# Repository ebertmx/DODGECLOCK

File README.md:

# DCLK_MK4

A shot clock system for competitve dodgeball. The system consists of two devices: display and controller.

## Status
This project is in progress...

### Controller
A first iteration PCB was order and successfully programmed. The firmware was tested with the MCU powered externally (without battery or linear regulator).

#### Problem with Linear Regulator
The BLE functionality on the PCB was not functional when powered by battery. Trouble shooting revealed the linear regulator is not acceptable for the current requirement of the antenna. Voltage spike when the antenna turns on crash the MCU.

A second iteration board is in progress to improve performance and fix the power delivery problems.

### Display
The display 7-segment frame was pritned with TPU and succesffuly passed all impact tests.
A nrf52 dongle will be used as the MCU for the display to save on time, costs, and assembly requirements.
The LED strip, power supply, and nrf52 dongle have been tested in a bench top environment succeffully.

## Description
### Controller
The controller device includes
- A PCB and MCU with BLE capabilities
- An LCD
- Several user inputs
- a buzzer

The controller devices is held by the ref and used to control the shot clock count. 

The device acts as a peripheral/server. It accepts secure connections and provide clock and state information. This device is battery powered; thus, it tries to mimize power at all times. The device prioritizes the built in LCD and user controls over the BLE connection; consequently, the ref always knows the correct shot clock time and can control the state.

### Display
The display device includes
- a WS2813B LED strip formed into a 7-segment pattern
- A PCB and MCU with BLE capablilities
- 2 user buttons for pairing and mode seletion
- A power supply

The display device is plugged into a wall outlet or similar power source and mounted within view of the court. The players and ref can reference this display. 

This device acts as a central/client. It initiates a secure connection with the controller and recieves time and state information if possible. If a connection is lost of cannot be estabilished it enters a dormant state and displays nothing. Otherwise, it displays the current count down time from the controller.

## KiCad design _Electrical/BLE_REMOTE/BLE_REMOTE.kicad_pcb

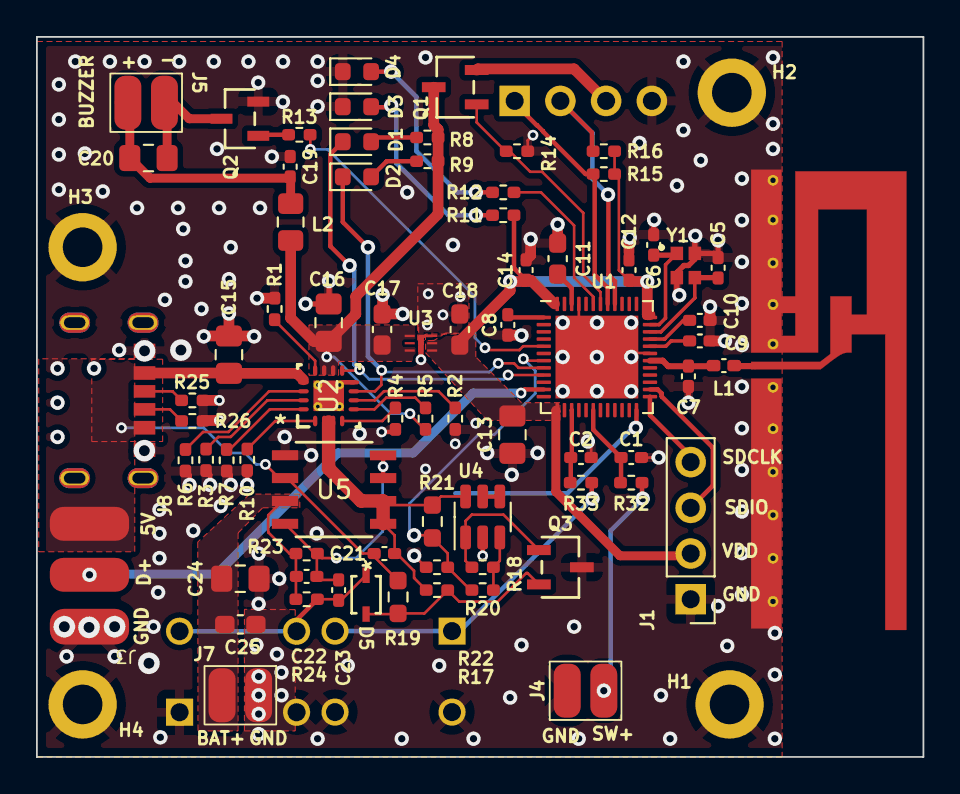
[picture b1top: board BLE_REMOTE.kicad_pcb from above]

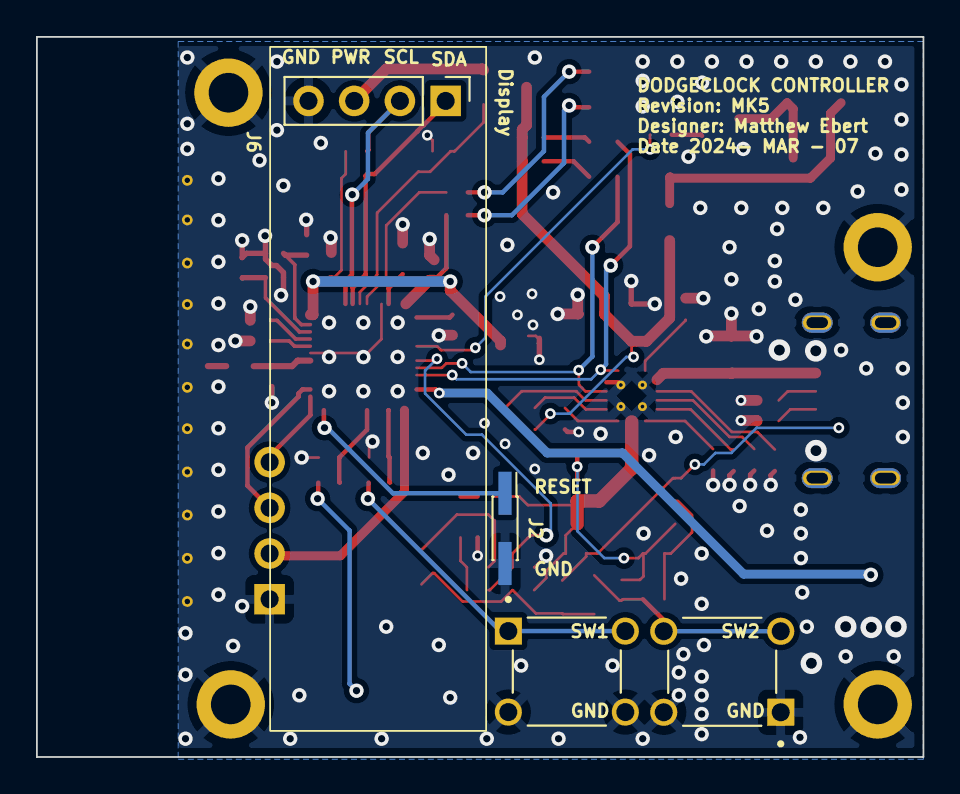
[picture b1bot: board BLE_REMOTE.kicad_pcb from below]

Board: 4 copper layers, 49.3 x 40.0 mm, 82 parts (4 on the bottom side), 54 nets.

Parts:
A1: SWRU120B
C1, C2, C21: 10uF; C_0402_1005Metric_Pad0.74x0.62mm_HandSolder
C5, C6: 10pF; C_0402_1005Metric_Pad0.74x0.62mm_HandSolder
C7: 0.8pF; C_0402_1005Metric_Pad0.74x0.62mm_HandSolder
C8, C12, C14, C22: 100nF; C_0402_1005Metric_Pad0.74x0.62mm_HandSolder
C9: NC; C_0402_1005Metric_Pad0.74x0.62mm_HandSolder
C10: 100pF; C_0402_1005Metric_Pad0.74x0.62mm_HandSolder
C11: 1uF; C_0603_1608Metric_Pad1.08x0.95mm_HandSolder
C13, C16, C20, C24: 4.7uF; C_0805_2012Metric_Pad1.18x1.45mm_HandSolder
C15: 1uF; C_0805_2012Metric_Pad1.18x1.45mm_HandSolder
C17, C18, C25: 2.2uF; C_0603_1608Metric_Pad1.08x0.95mm_HandSolder
C19: 1nF; C_0402_1005Metric_Pad0.74x0.62mm_HandSolder
C23: 1uF; C_0402_1005Metric_Pad0.74x0.62mm_HandSolder
D1, D2, D3, D4: LED; LED_0603_1608Metric
D5: 1N4148WX-TP; CR_SOD323_MCC-L
H1, H2, H3, H4: MountingHole_Pad; MountingHole_2.2mm_M2_DIN965_Pad
J1: PGRM; PinHeader_1x04_P2.54mm_Vertical
J2: RESET; PinHeader_2x01_P1.27mm_Vertical_SMD
J3: LED_STRIP; 3pad_conn
J4: SWITCH; 2pad_conn_sm
J5: BUZZER; 2pad_conn_sm
J6: Display; OLED_091
J7: Battery; 2pad_conn_sm
J8: USBC; GCT_USB4125-GF-A_REVA2
L1: 3.8nH; L_0402_1005Metric_Pad0.77x0.64mm_HandSolder
L2: 10uH; L_0805_2012Metric_Pad1.15x1.40mm_HandSolder
Q1: BSS806NEH6327XTSA1; SOT-23-3L_AOS
Q2: NPN; TRAN_SS8050-G_CIP
Q3: PMOS; SOT-23-3L_AOS
R1: 2.94k; R_0402_1005Metric_Pad0.72x0.64mm_HandSolder
R2, R3, R4, R5, R6: 0R; R_0402_1005Metric_Pad0.72x0.64mm_HandSolder
R7: 4.32k; R_0402_1005Metric_Pad0.72x0.64mm_HandSolder
R8, R9, R11, R12, R32, R33: 2k; R_0402_1005Metric_Pad0.72x0.64mm_HandSolder
R10, R24: 10k; R_0402_1005Metric_Pad0.72x0.64mm_HandSolder
R13: 220; R_0402_1005Metric_Pad0.72x0.64mm_HandSolder
R14, R15, R16: 47k; R_0402_1005Metric_Pad0.72x0.64mm_HandSolder
R17, R18, R22, R23: 100k; R_0402_1005Metric_Pad0.72x0.64mm_HandSolder
R19: 300k; R_0603_1608Metric_Pad0.98x0.95mm_HandSolder
R20: 1k; R_0402_1005Metric_Pad0.72x0.64mm_HandSolder
R21: 150k; R_0603_1608Metric_Pad0.98x0.95mm_HandSolder
R25, R26: 5.1k; R_0402_1005Metric_Pad0.72x0.64mm_HandSolder
SW1, SW2: SW_Push; SW_TS02-66-120-BK-260-LCR-D
U1: nRF52832-QFxx; QFN-48-1EP_6x6mm_P0.4mm_EP4.6x4.6mm
U2: BQ24232RGTR; RGT0016C
U3: MIC5528-3.3YMT-TR; TDFN6_1P2X1P2_MCH
U4: MCP65R41; SOT-23-6
U5: IRF7319TRPBF; TRANS_IRF7103TRPBF_INF
Y1: Crystal_GND24; OSC_XRCGB32M000F2P01R0

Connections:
+5V: C15.1, C21.2, J3.3, J8.A9 (VBUS), J8.B9 (VBUS__1), R19.2, U2.13 (IN), U5.2 (G1)
/MCU/ANT: C7.1, L1.2, U1.30 (ANT)
/MCU/RESET: J2.1, U1.24 (P0.21/~RESET)
/MCU/SWDCLK: J1.4, U1.25 (SWDCLK)
/MCU/SWDIO: J1.3, U1.26 (SWDIO)
/Peripherals/BUZZ+: C19.1, C20.1, J5.2, L2.2
/Peripherals/DIS_PWR: J6.3, Q1.2 (S)
/Power/BQ_CE_N: R4.1, U2.4 (CE_N)
/Power/BQ_EN1: R2.2, U2.6 (EN1)
/Power/BQ_EN2: R5.1, U2.5 (EN2)
/Power/BQ_ILIM: R1.2, U2.12 (ILIM)
/Power/BQ_ISET: R7.2, U2.16 (ISET)
/Power/BQ_ITERM: R3.1, U2.15 (ITERM)
/Power/BQ_TMR: R6.1, U2.14 (TMR)
/Power/BQ_TS: R10.1, U2.1 (TS)
/Power/Battery/BAT+: C22.1, C24.1, C25.1, J7.2, R23.2, R24.2, U5.3 (S2)
/Power/Battery/BAT_CTRL: D5.2 (A), Q3.2 (S), R17.2, R19.1
/Power/Battery/VBAT: C21.1, R17.1, R21.1, U2.2 (BAT), U2.3 (BAT), U4.6 (V+), U5.5 (D2), U5.6 (D2)
/Power/Battery/VREF: U4.4 (-), U4.5 (Vref)
BUTTON: C2.2, R33.2, U1.15 (P0.12)
BUZZ: R13.1, U1.5 (P0.03/AIN1)
CHG_N: D1.1 (K), U1.9 (P0.07), U2.9 (CHG_N)
DIS_EN: Q1.1 (G), R14.2, U1.42 (P0.30/AIN6)
DIS_SCL: J6.2, R16.1, U1.40 (P0.28/AIN4)
DIS_SDA: J6.1, R15.1, U1.41 (P0.29/AIN5)
GND: A1.2 (GND), A1.4, A1.5, C1.1, C2.1, C5.2, C6.1, C7.2, C8.2, C9.2, C10.2, C11.2, C12.1, C13.1, C14.1, C15.2, C16.2, C17.2, C18.2, C19.2, C24.2, C25.2, D3.1 (K), D4.1 (K), H1.1, H2.1, H3.1, H4.1, J1.1, J2.2, J3.1, J4.1, J6.4, J7.1, J8.A12 (GND), J8.B12 (GND__1), J8.S1 (SHIELD), J8.S2 (SHIELD__1), J8.S3 (SHIELD__2), J8.S4 (SHIELD__3), Q2.2, Q3.3 (D), R1.1, R2.1, R3.2, R4.2, R6.2, R7.1, R10.2, R14.1, R22.2, R25.1, R26.1, SW1.3, SW1.4, SW2.1, SW2.2, U1.31 (VSS), U1.45 (VSS), U1.49 (VSS), U2.8 (VSS), U2.17 (EP), U2.V, U3.3 (GND), U3.7 (EPAD), U4.2 (V-), U5.1 (S1), Y1.2, Y1.4
LED_D: J3.2, U1.11 (NFC1/P0.09)
unnamed: A1.1 (SIG), L1.1
unnamed: D1.2 (A), R8.2
unnamed: D2.2 (A), R9.2
unnamed: D3.2 (A), R11.2
unnamed: D4.2 (A), R12.2
unnamed: C23.2, D5.1 (K), R24.1, SW2.3, SW2.4
unnamed: J4.2, R32.1
unnamed: C20.2, J5.1, Q2.3
unnamed: J8.A5 (CC1), R25.2
unnamed: J8.B5 (CC2), R26.2
unnamed: Q2.1, R13.2
unnamed: Q3.1 (G), R18.2, U4.1
unnamed: R33.1, SW1.1, SW1.2
unnamed: C8.1, U1.1 (DEC1)
unnamed: C9.1, U1.32 (DEC2)
unnamed: C10.1, U1.33 (DEC3)
unnamed: C11.1, U1.46 (DEC4)
unnamed: C5.1, U1.34 (XC1), Y1.3
unnamed: C6.2, U1.35 (XC2), Y1.1
unnamed: R18.1, R20.2, U4.3 (+)
unnamed: C22.2, C23.1, R23.1, U5.4 (G2), U5.7 (D1), U5.8 (D1)
PGOOD_N: D2.1 (K), U1.8 (P0.06), U2.7 (PGOOD_N)
SWITCH: C1.2, R32.2, U1.18 (P0.15)
TEST_BAT: R20.1, R21.2, R22.1, U1.7 (P0.05/AIN3)
USER: R12.1, U1.43 (P0.31/AIN7)
VCC: C16.1, C17.1, L2.1, Q1.3 (D), R5.2, R8.1, R9.1, U2.10 (OUT), U2.11 (OUT), U3.4 (EN), U3.6 (VIN)
VDD: C12.2, C13.2, C14.2, C18.1, J1.2, R11.1, R15.2, R16.2, U1.13 (VDD), U1.36 (VDD), U1.48 (VDD), U3.1 (VOUT), U3.2 (VOUT)

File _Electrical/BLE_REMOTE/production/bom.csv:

Designator,Footprint,Quantity,Value,LCSC Part #
A1,SWRU120B,1,SWRU120B,
"C1, C2, C21",0402,3,10uF,C15525
C10,0402,1,100pF,C1546
C11,0603,1,1uF,C15849
"C12, C14, C22, C8",0402,4,100nF,C1525
"C13, C16, C20, C24",0805,4,4.7uF,C1779
C15,0805,1,1uF,C28323
"C17, C18, C25",0603,3,2.2uF,C23630
C19,0402,1,1nF,C1523
C23,0402,1,1uF,C52923
"C5, C6",0402,2,10pF,C32949
C7,0402,1,0.8pF,C327032
C9,0402,1,NC,
"D1, D2, D3, D4",0603,4,LED,C2286
D5,CR_SOD323_MCC-L,1,1N4148WX-TP,C2128
J5,2pad_conn_sm,1,BUZZER,C2759981
J8,GCT_USB4125-GF-A_REVA2,1,USBC,
L1,0402,1,3.8nH,C412343
L2,0805,1,10uH,C1046
Q1,SOT-23-3L_AOS,1,BSS806NEH6327XTSA1,C20917
Q2,TRAN_SS8050-G_CIP,1,NPN,C2150
Q3,SOT-23-3L_AOS,1,PMOS,C15127
R1,0402,1,2.94k,C273724
"R10, R24",0402,2,10k,C25744
"R11, R12, R32, R33, R8, R9",0402,6,2k,C4109
R13,0402,1,220,C25091
"R14, R15, R16",0402,3,47k,C25792
"R17, R18, R22, R23",0402,4,100k,C25741
R19,0603,1,300k,C23024
"R2, R3, R4, R5, R6",0402,5,0R,C17168
R20,0402,1,1k,C11702
R21,0603,1,150k,C22807
"R25, R26",0402,2,5.1k,C25905
R7,0402,1,4.32k,C334698
"SW1, SW2",SW_TS02-66-120-BK-260-LCR-D,2,SW_Push,
U1,QFN-48-1EP_6x6mm_P0.4mm_EP4.6x4.6mm,1,nRF52832-QFxx,C77540
U2,RGT0016C,1,BQ24232RGTR,C528622
U3,TDFN6_1P2X1P2_MCH,1,MIC5528-3.3YMT-TR,C622490
U4,SOT-23-6,1,MCP65R41,C219181
U5,TRANS_IRF7103TRPBF_INF,1,IRF7319TRPBF,C5123893
Y1,OSC_XRCGB32M000F2P01R0,1,Crystal_GND24,C2901738

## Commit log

2023-12-23 Reorganized Modules
2023-12-24 Pair with "Just Works"
    Removed the authentication since devices will not have appropriate displays for BLE SMP level 3 or 4
2023-12-24 Both Display and Remote
    Connection estabilished but no pairing yet
2023-12-25 Fixed folder and file organization
2023-12-25 Renamed folder
2023-12-25 deleted build directory
2023-12-27 Add level 4 fixed passkey security# Please enter the commit message for your changes. Lines starting
2023-12-28 We have lift off, subsription with level 4 security for DCLK service
2024-01-02 Reoganized and deleted extraneous code
2024-01-03 finished reorganized and updated subscription functionality
2024-01-03 Not functional; need to fix bond saving.
2024-01-03 Adjusted LOG output and redefined callbacks
2024-01-03 Reconnect is functional after either power disconnect
2024-01-04 Updated security callbacks
2024-01-05 Does not work, Saving
2024-01-05 Fixed security issues and addressed save BLE connections
2024-01-06 improved security and bonding functionality of Controller
2024-01-06 Connection/Pairing for single device achieved.k
2024-01-08 adjusting memory usage to fit in 810
2024-01-08 DCLK Service working on custom nrf52810 board
2024-01-08 Pairing possible, need to deal with memory and RAM shortage
2024-01-09 recovered some RAM space by reducing work and rx stacks
2024-01-09 Achieved pairing and notification with smaller stack
2024-01-09 ready for merge
2024-01-10 interrupts and work handler working for buttons; NVS
2024-01-12 renamed conf
2024-01-19 Display working on nRF52 DK
2024-01-19 Buzzer working
2024-01-19 added pairing indication
2024-01-19 added information callbacks and control functionality.
2024-01-19 works on dongle
2024-02-29 Added electrical first draft
2024-02-29 Began simulation and circuit for power switch
2024-03-01 Added simulation and updated power button
2024-03-01 fixed simulation and added documentation
2024-03-05 started PCB design
2024-03-05 uploading stash
2024-03-05 PCB parts placed
2024-03-06 Finished initial PCB draft
2024-03-06 read last
2024-03-06 second iteration PCB layout
2024-03-07 JLCPCB parts selected
2024-03-07 added part files
2024-03-07 Adjusted components and changed buttons
2024-03-11 asdasat
2024-03-12 ordered from JLCPCB
2024-05-23 uploading unkown stash
2024-05-23 compile for nrf52 dk. Removed pwm check
2024-05-31 Revert "compile for nrf52 dk. Removed pwm check"
    This reverts commit 1a2fb9181a95703c27e4ce2f10d252ffe28e0c90.
2024-05-31 Revert "uploading unkown stash"
    This reverts commit 6120b71af1dbd9c259f19d39c2f2662de9dc6992.
2024-05-31 created proto functionality using hrs
2024-05-31 added bonding requirement with passkey
2024-05-31 enabled flash to store bond information
2024-06-01 created initial bond, pairing, and connection functionality
2024-06-01 enabled RTT, added logic for connection handling. Current error with comparing connections
2024-06-05 added filter accept list functionality
2024-06-06 saving
2024-06-06 Revert "added filter accept list functionality"
    This reverts commit b85f57d3c8de066d81093106345f02d7e72b3fa5.
2024-06-06 Revert "enabled RTT, added logic for connection handling. Current error with" This reverts commit 4af11d224467d091882f2f85c517c035bca3143f.
2024-06-06 Revert "Revert "enabled RTT, added logic for connection handling. Current error with""
    This reverts commit b1e8c4c9b3f6cb85fef86c90e8f08ce3f5824af5.
2024-06-06 Revert "Revert "added filter accept list functionality""
    This reverts commit 20e23b1b6a22b2c05ddf5c3fbc5df48df601624a.
2024-06-06 Revert "Revert "Revert "added filter accept list functionality"""
    This reverts commit d2567a696ef4ca2b97447a1e4271306028ed3c4b.
2024-06-06 fixed filter list and reconnect. Need to disable advertising on reconnect
2024-06-18 added bt connection manager task
2024-06-18 implemented sec change and pair manager options
2024-06-18 changed manager to use OOP style
